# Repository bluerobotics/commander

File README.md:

# Commander

Blue Robotics Thruster Commander hardware and software: Thruster Test Jig Version.

Acceleration is limited more in this version than is usual.  Changing speed from stopped to full speed takes 2.0 seconds (as opposed to 0.8 seconds for the default firmware).

## Compiling and Uploading

The code can be compiled in the Arduino IDE version 1.0 and above. It requires the `attiny` board plugin by David Mellis, which can be installed with the Arduino Boards Manager. The following compile settings should be used:

- **Board:** ATtiny
- **Processor:** ATtiny84
- **Clock:** 8 Mhz (External)

- **Programmer:** USBTinyISP (or whatever you're using)

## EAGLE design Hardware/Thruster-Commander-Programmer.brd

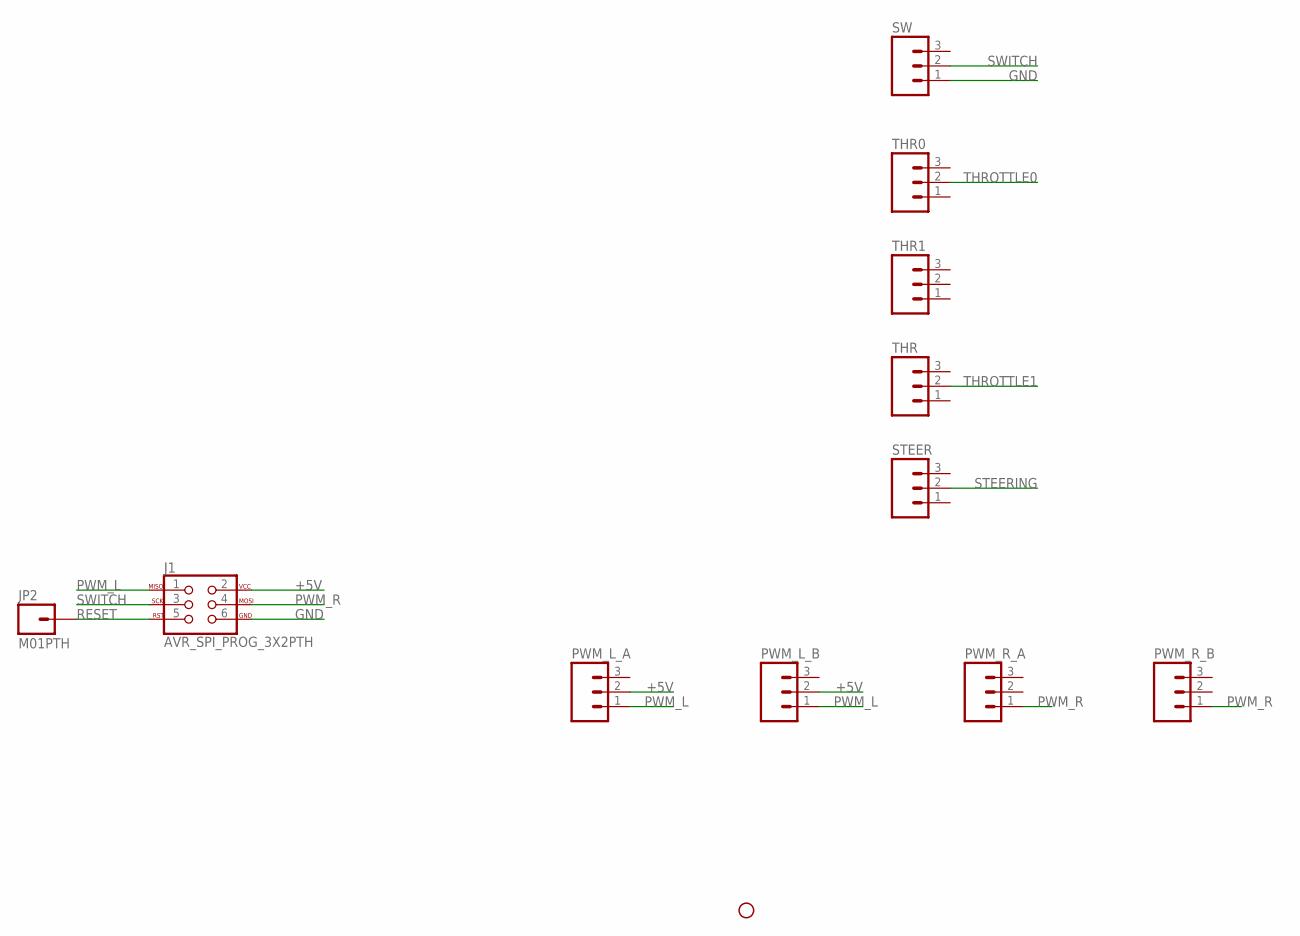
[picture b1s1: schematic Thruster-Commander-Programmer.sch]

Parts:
J1: AVR_SPI_PROG_3X2PTH; 2X3
JP2: M01PTH; 1X01
PWM_L_A: M03PTH; 1X03
PWM_L_B: M03PTH; 1X03
PWM_R_A: M03PTH; 1X03
PWM_R_B: M03PTH; 1X03
STANDOFF1: STAND-OFF
STEER: M03PTH; 1X03
SW: M03PTH; 1X03
THR, THR0, THR1: M03PTH; 1X03

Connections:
+5V: J1.2, PWM_L_A.2, PWM_L_B.2
GND: J1.6, SW.1
PWM_L: J1.1, PWM_L_A.1, PWM_L_B.1
PWM_R: J1.4, PWM_R_A.1, PWM_R_B.1
RESET: J1.5, JP2.1
STEERING: STEER.2
SWITCH: J1.3, SW.2
THROTTLE0: THR0.2
THROTTLE1: THR.2

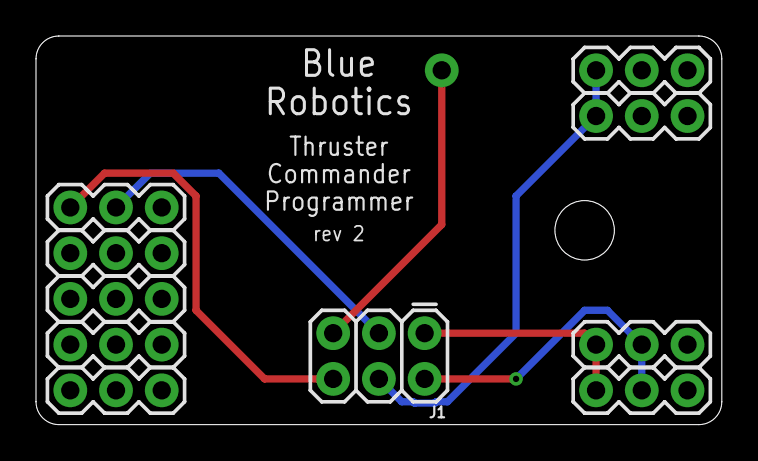
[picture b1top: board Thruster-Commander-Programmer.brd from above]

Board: 2 copper layers, 38.1 x 21.6 mm, 12 parts (1 on the bottom side), 6 nets.

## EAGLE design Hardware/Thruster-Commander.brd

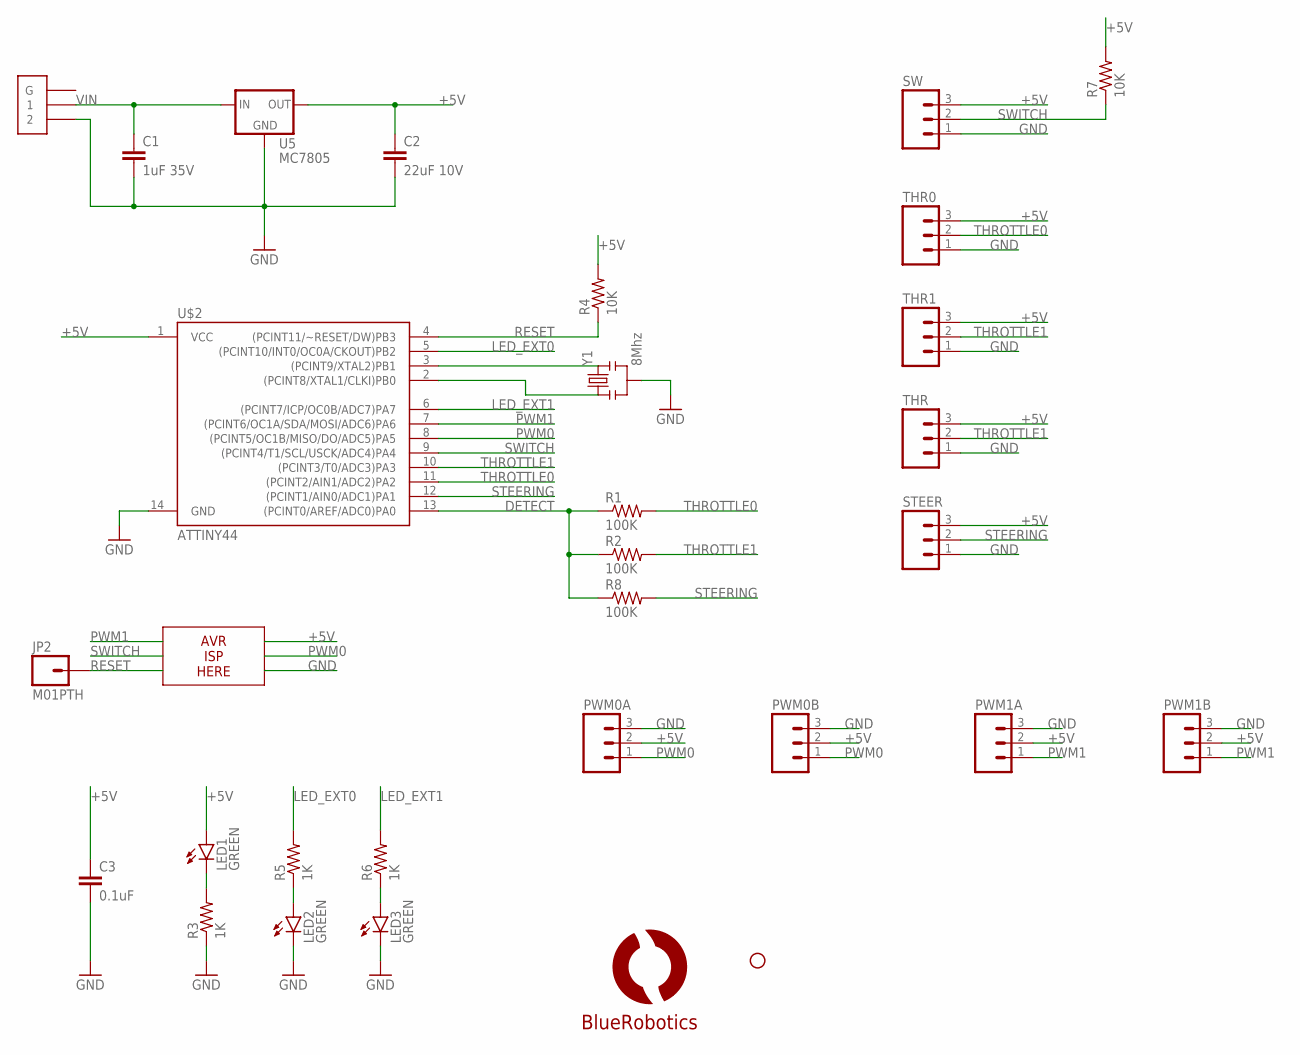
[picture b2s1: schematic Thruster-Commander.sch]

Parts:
C1: 1uF 35V; 0603-CAP
C2: 22uF 10V; 1206
C3: 0.1uF; 0603-CAP
JP2: M01PTH; 1X01
LED1, LED2, LED3: GREEN; LED-0603
PWM0A, PWM0B, PWM1A, PWM1B: M03PTH; 1X03
R1, R2, R8: 100K; 0603-RES
R3, R5, R6: 1K; 0603-RES
R4, R7: 10K; 0603-RES
STANDOFF1: STAND-OFF
STEER: M03PTH; 1X03
SW: M03PTH; 1X03
THR, THR0, THR1: M03PTH; 1X03
U5: MC7805; DPAK
U$1: LOGOBR-LOGO-MS; BR-LOGO-MEDIUM-SMALL
U$2: ATTINY44; SO14
U$3: JSH-GH-2VERT; JST-GH-TOP-2
Y1: 8Mhz; RESONATOR-SMD

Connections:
+5V: C2.1, C3.1, LED1.A, PWM0A.2, PWM0B.2, PWM1A.2, PWM1B.2, R4.2, R7.2, STEER.3, SW.3, THR.3, THR0.3, THR1.3, U5.3 (OUT), U$2.1 (VCC)
DETECT: R1.1, R2.1, R8.1, U$2.13 ((PCINT0/AREF/ADC0)PA0)
GND: C1.2, C2.2, C3.2, LED2.C, LED3.C, PWM0A.3, PWM0B.3, PWM1A.3, PWM1B.3, R3.1, STEER.1, SW.1, THR.1, THR0.1, THR1.1, U5.4 (GND), U$2.14 (GND), U$3.2, Y1.2
LED_EXT0: R5.2, U$2.5 ((PCINT10/INT0/OC0A/CKOUT)PB2)
LED_EXT1: R6.2, U$2.6 ((PCINT7/ICP/OC0B/ADC7)PA7)
unnamed: LED1.C, R3.2
unnamed: LED2.A, R5.1
unnamed: U$2.3 ((PCINT9/XTAL2)PB1), Y1.3
unnamed: U$2.2 ((PCINT8/XTAL1/CLKI)PB0), Y1.1
unnamed: LED3.A, R6.1
PWM0: PWM0A.1, PWM0B.1, U$2.8 ((PCINT5/OC1B/MISO/DO/ADC5)PA5)
PWM1: PWM1A.1, PWM1B.1, U$2.7 ((PCINT6/OC1A/SDA/MOSI/ADC6)PA6)
RESET: JP2.1, R4.1, U$2.4 ((PCINT11/~RESET/DW)PB3)
STEERING: R8.2, STEER.2, U$2.12 ((PCINT1/AIN0/ADC1)PA1)
SWITCH: R7.1, SW.2, U$2.9 ((PCINT4/T1/SCL/USCK/ADC4)PA4)
THROTTLE0: R1.2, THR0.2, U$2.11 ((PCINT2/AIN1/ADC2)PA2)
THROTTLE1: R2.2, THR.2, THR1.2, U$2.10 ((PCINT3/T0/ADC3)PA3)
VIN: C1.1, U5.1 (IN), U$3.1

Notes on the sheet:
AVR ISP HERE

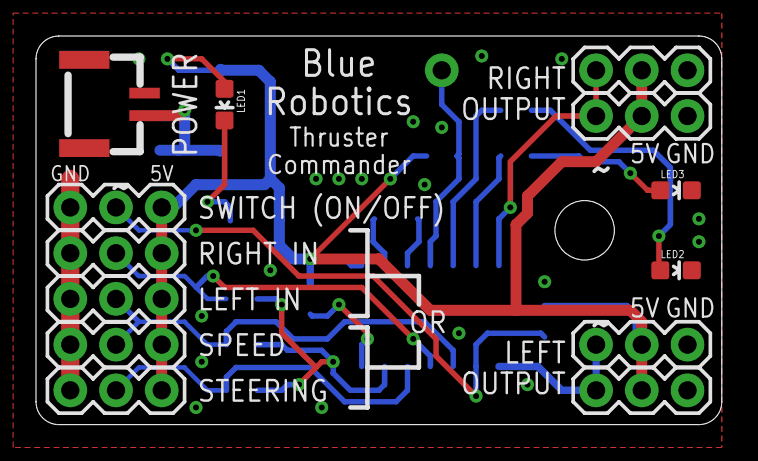
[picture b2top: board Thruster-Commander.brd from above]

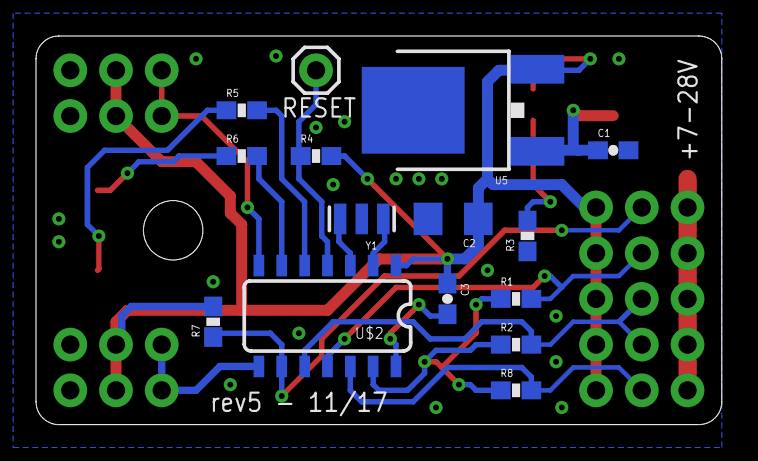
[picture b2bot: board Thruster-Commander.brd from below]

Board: 2 copper layers, 38.1 x 21.6 mm, 30 parts (15 on the bottom side), 18 nets.

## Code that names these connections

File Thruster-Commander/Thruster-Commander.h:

/* Blue Robotics Thruster Commander Firmware
-----------------------------------------------------

Title: Blue Robotics Thruster Commander Firmware

Description: This code is the default firmware for the Blue Robotics
Thruster Commander, which provides a simple interface to control a
bidirectional speed controller with PWM signals. It can be used to test
motors or to control simple vehicles like a kayak.

The code is designed for the ATtiny84 microcontroller and can be compiled and
uploaded via the Arduino 1.0+ software.

-------------------------------
The MIT License (MIT)

Copyright (c) 2017 Blue Robotics Inc.

Permission is hereby granted, free of charge, to any person obtaining a copy
of this software and associated documentation files (the "Software"), to deal
in the Software without restriction, including without limitation the rights
to use, copy, modify, merge, publish, distribute, sublicense, and/or sell
copies of the Software, and to permit persons to whom the Software is
furnished to do so, subject to the following conditions:

The above copyright notice and this permission notice shall be included in
all copies or substantial portions of the Software.

THE SOFTWARE IS PROVIDED "AS IS", WITHOUT WARRANTY OF ANY KIND, EXPRESS OR
IMPLIED, INCLUDING BUT NOT LIMITED TO THE WARRANTIES OF MERCHANTABILITY,
FITNESS FOR A PARTICULAR PURPOSE AND NONINFRINGEMENT. IN NO EVENT SHALL THE
AUTHORS OR COPYRIGHT HOLDERS BE LIABLE FOR ANY CLAIM, DAMAGES OR OTHER
LIABILITY, WHETHER IN AN ACTION OF CONTRACT, TORT OR OTHERWISE, ARISING FROM,
OUT OF OR IN CONNECTION WITH THE SOFTWARE OR THE USE OR OTHER DEALINGS IN
THE SOFTWARE.
-------------------------------*/

#ifndef THRUSTERCOMMANDER
#define THRUSTERCOMMANDER

#include <Arduino.h>

// HARDWARE PIN DEFINITIONS
#define INPUT_L     A3  // Left In
#define INPUT_R     A2  // Right In
#define INPUT_SPD   A3  // Speed
#define INPUT_STR   A1  // Steering
#define SWITCH      4
#define PWM_L       5
#define PWM_R       6
#define LED_L       8
#define LED_R       7
#define DETECT      0

// PWM GENERATION DEFINITIONS
#define PWM_FREQ    50                // Hz
#define PERIOD      1000000/PWM_FREQ  // us
#define PRESCALE    8                 // must match TCCR1B settings
#define CLOCK_FREQ  8000000ul         // Hz
#define CNT_PER_US  1                 // CLOCK_FREQ/PRESCALE/1000000 timer counts

// PWM OUTPUT CHARACTERISTICS
#define PWM_MAX     2000              // us
#define PWM_MIN     1000              // us
#define PWM_NEUTRAL 1500              // us
#define STEER_MAX   400               // us
#define HALF_RANGE  500               // us
#define DEADZONE    25                // us
#define POT_OFFSET  -12               // adc counts

// DETECT PARAMETERS
#define DETECT_LOW  20                // adc counts
#define DETECT_HIGH 1003              // adc counts

// BLINKER CHARACTERISTICS
#define PERIOD_MIN  200               // ms
#define PERIOD_MAX  2000              // ms

// ACCELERATION CONTROL
#define MAX_ACCEL   (HALF_RANGE/2.0f) // us/s

// PWM UPDATE RATE
#define UPDATE_DT   0.050f            // s

// DETECT RATE
#define DETECT_DT   0.250f            // s

#endif

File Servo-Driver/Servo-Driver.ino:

//#include <avr/io.h>
//#include <avr/interrupt.h>

// HARDWARE PIN DEFINITIONS
#define INPUT_INT   A1
#define INPUT_EXT0  A2
#define INPUT_EXT1  A3
#define PWM_0       6
#define PWM_1       5
#define LED_INT     4
#define LED_EXT0    8
#define LED_EXT1    7
#define DETECT      0

// PWM GENERATION DEFINITIONS
#define PWM_FREQ    50                // Hz
#define PERIOD      1000000/PWM_FREQ  // us
#define PRESCALE    8                 // must match TCCR1B settings
#define CLOCK_FREQ  8000000ul         // Hz
#define CNT_PER_US  1                 // CLOCK_FREQ/PRESCALE/1000000 timer counts

bool ext0IsConnected, ext1IsConnected;
int pwmOut0, pwmOut1;

void setup() {
  // Set up pin modes
  pinMode(INPUT_INT,INPUT);
  pinMode(INPUT_EXT0,INPUT);
  pinMode(INPUT_EXT1,INPUT);
  pinMode(LED_INT,OUTPUT);
  pinMode(LED_EXT0,OUTPUT);
  pinMode(LED_EXT1,OUTPUT);
  pinMode(PWM_0,OUTPUT);
  pinMode(PWM_1,OUTPUT);

  digitalWrite(LED_INT,HIGH);
  delay(200);
  digitalWrite(LED_INT,LOW);
  delay(200);

  // Set PWM output (temporary)
  pwmOut0 = 1500;
  pwmOut1 = 1500;

  // Stop interrupts while changing timer settings
  cli();

  // Set timer1 control register A/B/C
  TCCR1A  = 0;
  TCCR1B  = 0;
  TCCR1C  = 0;

  // Set non-inverting Fast PWM mode on A and B
  TCCR1A |= (1 << COM1A1);
  TCCR1A |= (1 << COM1B1);
  // Set Fast PWM mode (compare to ICR1)
  TCCR1A |= (1 << WGM11);
  TCCR1B |= (1 << WGM12);
  TCCR1B |= (1 << WGM13);
  // Set timer1 clock source to prescaler 8
  TCCR1B |= (1 << CS11);

  // Set timer1 Input Capture Register
  // Set end counter value to get a PWM_FREQ Hz timer
  ICR1    = (PERIOD  * CNT_PER_US) - 1;
  
  // Set timer1 Output Compare Register A
  // Set shut-off counter value to get pwmOut0 pulse
  OCR1A   = (pwmOut0 * CNT_PER_US) - 1;

  // Set timer1 Output Compare Register B
  // Set shut-off counter value to get pwmOut pulse
  OCR1B   = (pwmOut1  * CNT_PER_US) - 1;
  
  // Done setting timers -> allow interrupts again
  sei();
}

void loop() {
  // put your main code here, to run repeatedly:
  digitalWrite(LED_INT,HIGH);
  delay(200);

  digitalWrite(LED_INT,LOW);
  delay(800);
}

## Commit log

2017-09-22 Initial files and readme.
2017-09-22 Type fix
2017-10-05 Directly use timers to control PWM
2017-10-06 Fix blinking lights
2017-10-10 Constrain pulse width
2017-10-10 Refactor code
2017-10-16 Correct midpoint offset on external pots
2017-10-16 rev3 version.
2017-10-20 Updates to rev4.
2017-10-20 Remove Servo-Driver test
2017-10-25 Add low-pass filters to pwm outputs
2017-11-01 Pin reassignment and function updates
2017-11-01 Change SWITCH to deadman mode
2017-11-01 Simplify detect
2017-11-01 Simplify writePWM functions
2017-11-01 Simplify filter
2017-11-01 Change Blinker to class
2017-11-03 rev5 hardware.
2017-11-06 Allow pot hot swap
2017-11-06 Use LED brightness to show speed, display errors as blink codes
2017-11-20 Style corrections
    Correct code to use java style with 2 spaces indentation and some pad conventions.
    This script can be used to correct future problems:
    - `astyle --unpad-paren --pad-header --indent=spaces=2 --style=java --pad-comma -R "${PWD}/*.h" "${PWD}/*.cpp" "${PWD}/*.ino"`
2017-11-28 Minor updates.
2017-11-28 Add programmer boards
2017-11-30 Do not initialize automatically on start
2017-11-30 Reduce firmware size
2017-11-30 Filter harder
2017-11-30 Remove hyphen from #define name
2017-11-30 Style corrections
2017-11-30 Update listed processor
2017-12-05 Replace low-pass filter with acceleration limiter
2017-12-08 Add programmer script
2017-12-08 Add binary
2017-12-08 Fix programmer board MISO/MOSI connections
2017-12-28 Fix programming script settings
2018-05-31 Fix errant pot detection when touching PCB
2018-05-31 Use time differences instead of timestamps for scheduling
2018-05-31 Update firmware .hex file
2018-06-07 Remove acceleration limiter
2018-06-07 Add button control
2018-08-22 Limit change in PWM to half range over 2 seconds (from 0.8)
2018-08-22 Add acceleration limit change note to README

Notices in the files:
parts and their libraries:
SparkFun-Connectors: Licensing: Creative Commons ShareAlike 4.0 International - https://creativecommons.org/licenses/by-sa/4.0
